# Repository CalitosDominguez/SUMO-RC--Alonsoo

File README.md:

# SUMO-RC--Alonsoo
sumo de combate controlado mediante un dispositivo

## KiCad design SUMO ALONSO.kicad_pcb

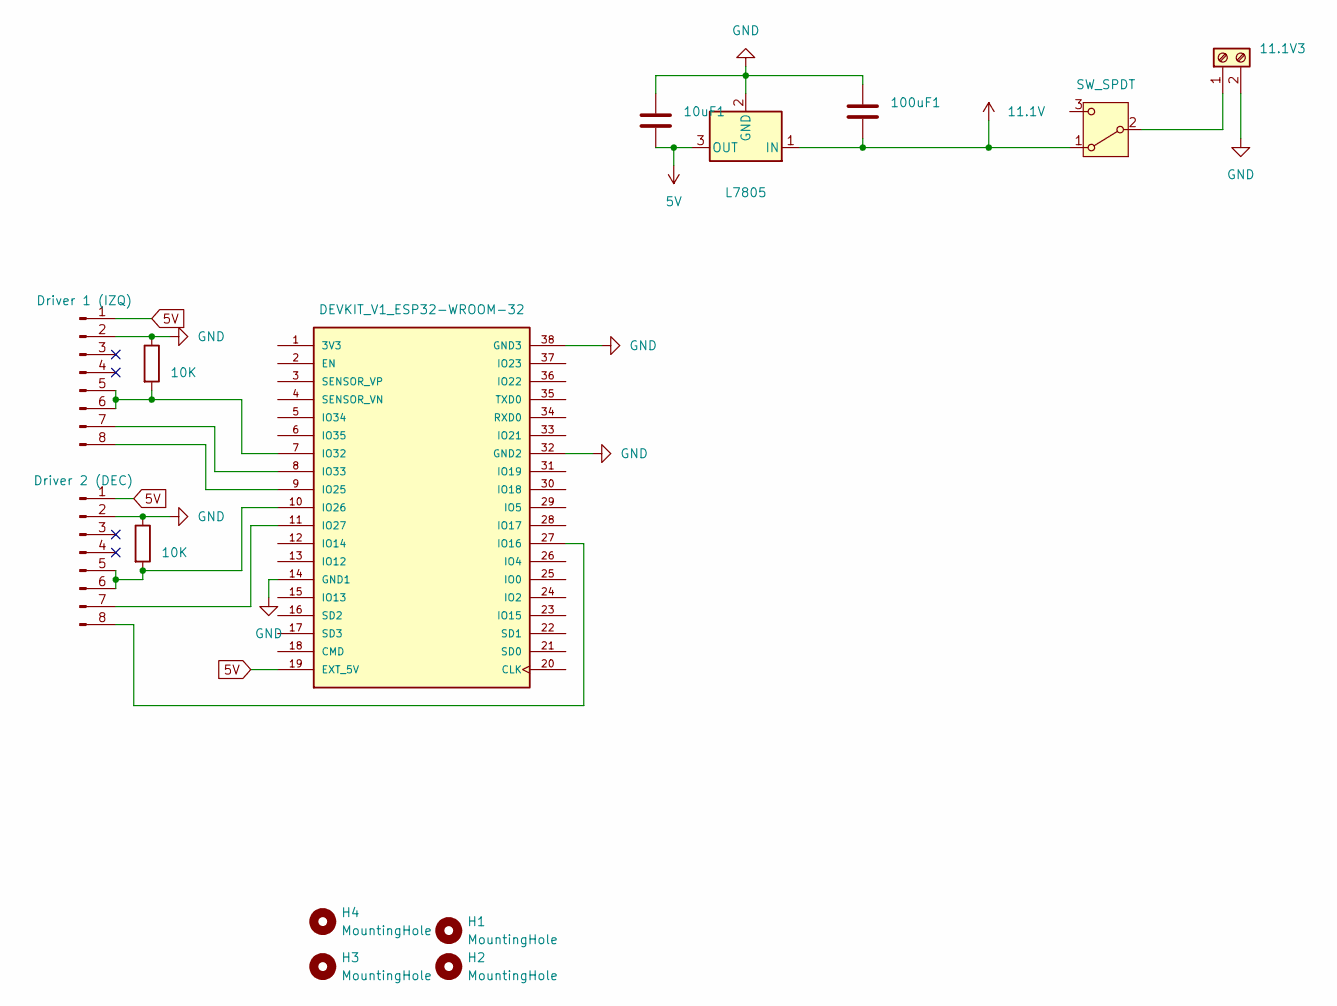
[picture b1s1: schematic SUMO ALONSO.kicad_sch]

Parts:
10uF1: 10uF; C_0805_2012Metric
11.1V3: TerminalBlock_MaiXu_MX126-5.0-02P_1x02_P5.00mm
100uF1: 100uF; C_0805_2012Metric
H1, H2, H3, H4: MountingHole; MountingHole_3.2mm_M3
J4: Driver 1 (IZQ); IDC-Header_2x04_P2.54mm_Vertical
J5: Driver 2 (DEC); IDC-Header_2x04_P2.54mm_Vertical
R1, R2: 10K; R_0805_2012Metric
SW1: SW_SPDT; SW_100SP1T6B11M1QE
U1: L7805; TO-220-3_Vertical
U3: DEVKIT_V1_ESP32-WROOM-32; MODULE_DEVKIT_V1_ESP32-WROOM-32; PARTREV N/A

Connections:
5V: 10uF1.2, J4.1, J5.1, U1.3 (OUT), U3.19 (EXT_5V)
11.1V: 100uF1.2, SW1.1 (A), U1.1 (IN)
GND: 10uF1.1, 11.1V3.2, 100uF1.1, J4.2, J5.2, R1.1, R2.1, U1.2 (GND), U3.14 (GND1), U3.32 (GND2), U3.38 (GND3)
unnamed: 11.1V3.1, SW1.2 (B)
unnamed: J4.5, J4.6, R1.2, U3.7 (IO32)
unnamed: J4.7, U3.8 (IO33)
unnamed: J4.8, U3.9 (IO25)
unnamed: J5.5, J5.6, R2.2, U3.10 (IO26)
unnamed: J5.7, U3.11 (IO27)
unnamed: J5.8, U3.27 (IO16)

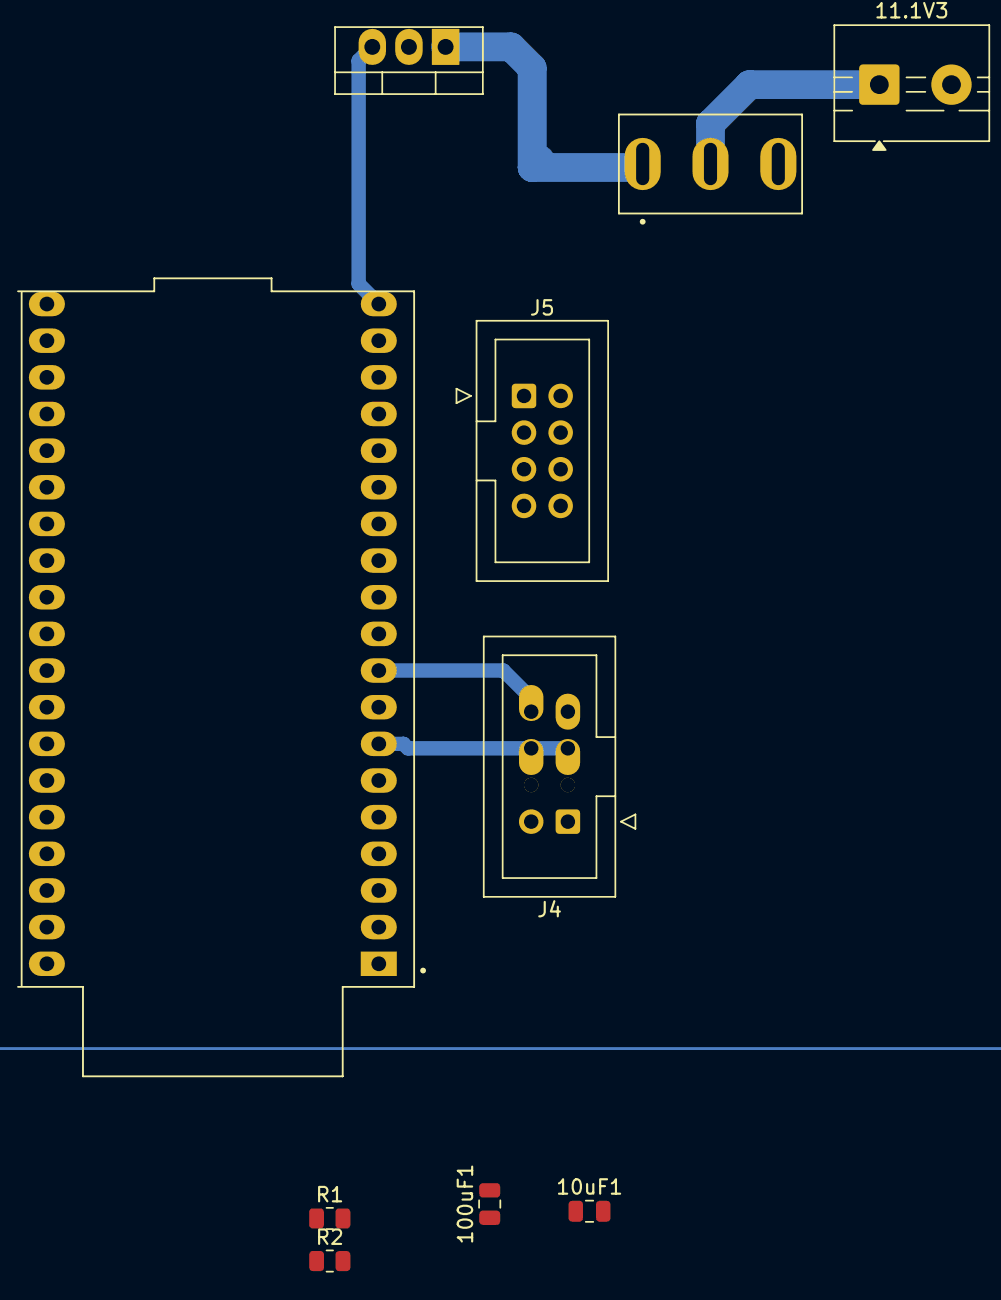
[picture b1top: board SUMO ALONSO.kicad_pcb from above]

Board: 2 copper layers, 14 parts (0 on the bottom side), 10 nets.

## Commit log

2026-05-08 Create SUMO Alonso RC DEFINITIVO
